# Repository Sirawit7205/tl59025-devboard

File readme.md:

# TLC59025 Devboard

This is an open-source KiCAD design files for a development for [Texas Instruments TLC59025](https://www.ti.com/lit/ds/symlink/tlc59025.pdf) 16-Channel Constant Current LED Driver (and clones).

## Pictures

## Features

This devboard provides full flexibility for testing various configurations of the chip and surrounding circuits.

- Support original and clones in QSOP-24 package:
	- TI TLC59025IDBQR
	- Macroblock MBI5124GP
	- Shenzhen Sunmoon SM16206S
	- Shenzhen Sunmoon SM16306S
	- Shenzhen Titan TM5020A
- Full control over the chip's functions:
	- Output LEDs on all output channels.
	- R-EXT trimpot on each chip for adjusting the sink current.
	- All control pins break out.
- Cascade design
	- Input and output headers provided for cascading of modules (allows single controller only).
- Multiple power options
	- USB Type-C
	- Input header (both regulated and unregulated)
	- Optional footprint for an LDO.
- Onboard Microcontroller
	- Optional footprint for ATtiny214/414/814.
	- A user button and several debug pads provided.
	- A CH340 bridge for serial communication with a computer.
	- UPDI Header included.
	- SerialUPDI support included.
	
## Revisions

We are currently at Revision 1. Changelog is below:

**Revision 1 (September 2022)**
 - Initial Design

## What is provided

The goal of this repository is to enable you to build this on your own as easy as possible (although I originally plan to sell this as a kit as well). **The schematics, PCB design, and an interactive BOM is provided.**

Hardware is licensed under `SPDX-License-Identifier: CERN-OHL-S-2.0`

Software is licensed under `SPDX-License-Identifier: GPL` (Actually there is no software for this board. Oops.)

Documentation is licensed under `SPDX-License-Identifier: CC-BY-SA-4.0`

**This project is an OSHWA Certified Open Source Hardware Project with UID [TH000010](https://certification.oshwa.org/th000010.html).**

3D models that are use to render the board in KiCAD is not included. They are all from GrabCad and you could search and download them by yourself.

## Third-Party 3D Models

- 6x3.5mm Tactile Button by Gabriel Tóth: https://grabcad.com/library/6x3-5mm-smd-tactile-button-1
- Bourns 3362P Trimpot by Markus Walter: https://grabcad.com/library/bourns-3362p-1-102lf
- USB Type-C port by Hamza Huzair: https://grabcad.com/library/usb-type-c-port-smd-type-1
 
 ## Ordering
 
 You can export gerbers from this project and order the board yourself. You can also use the link below to directly order from Aisler.
 https://aisler.net/p/IMLSHTDQ

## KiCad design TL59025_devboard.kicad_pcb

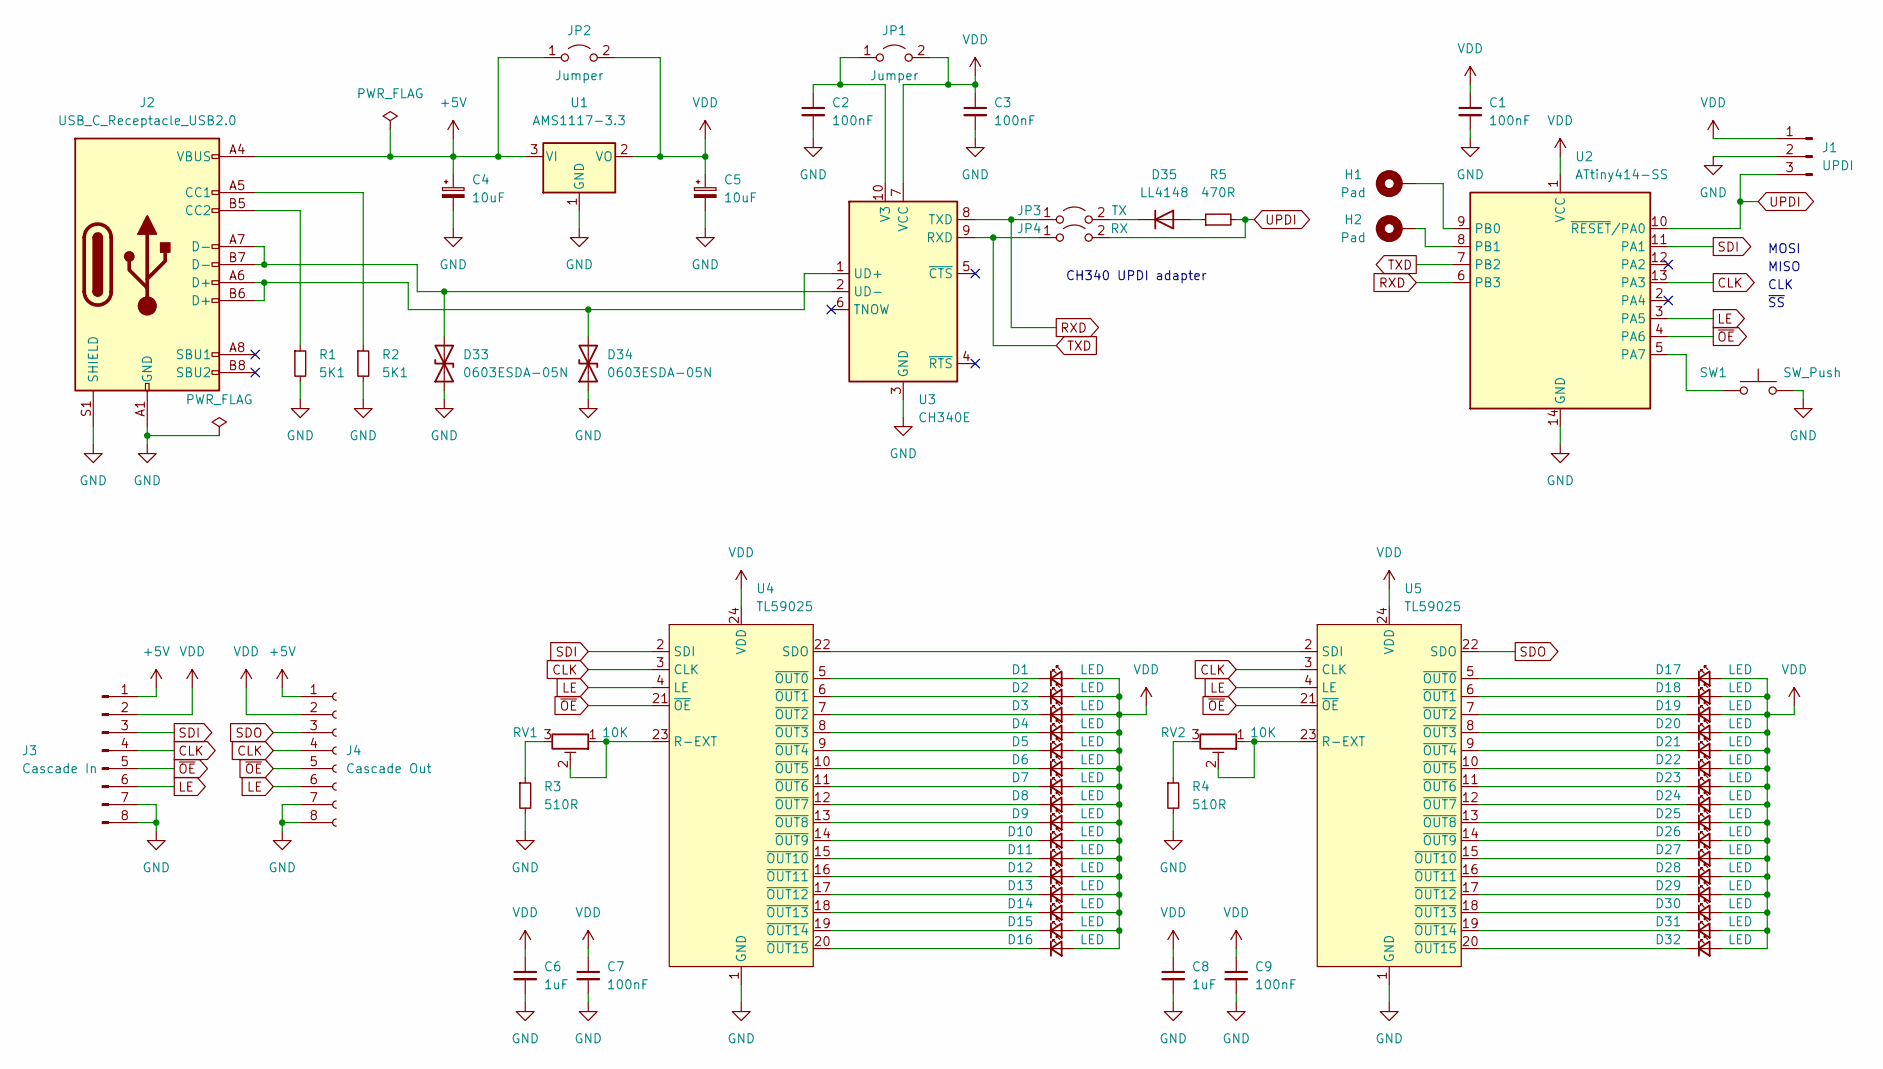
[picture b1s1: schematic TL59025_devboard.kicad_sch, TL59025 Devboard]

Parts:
C1, C2, C3, C7, C9: 100nF; C_0603_1608Metric
C4, C5: 10uF; CP_Radial_D5.0mm_P2.00mm
C6, C8: 1uF; C_0603_1608Metric
D1, D2, D3, D4, D5, D6, D7, D8, D9, D10, D11, D12, D13, D14, D15, D16, D17, D18, D19, D20, D21, D22, D23, D24, D25, D26, D27, D28, D29, D30, D31, D32: LED; LED_0805_2012Metric
D33, D34: 0603ESDA-05N; D_0603_1608Metric
D35: LL4148; D_MiniMELF
H1, H2: Pad; TestPoint_Pad_D1.0mm
J1: UPDI; PinHeader_1x03_P2.54mm_Vertical
J2: USB_C_Receptacle_USB2.0; USB_C_Receptacle_HRO_TYPE-C-31-M-12_NO_SBU_CircularHoles
J3: Cascade In; PinHeader_1x08_P2.54mm_Vertical
J4: Cascade Out; PinSocket_1x08_P2.54mm_Vertical
JP1, JP2: Jumper; SolderJumper-2_P1.3mm_Open_Pad1.0x1.5mm
JP3: TX; PinHeader_1x02_P2.54mm_Vertical
JP4: RX; PinHeader_1x02_P2.54mm_Vertical
R1, R2: 5K1; R_0603_1608Metric
R3, R4: 510R; R_0603_1608Metric
R5: 470R; R_0603_1608Metric
RV1, RV2: 10K; 3362P_1
SW1: SW_Push; TS-1101
U1: AMS1117-3.3; SOT-223-3_TabPin2
U2: ATtiny414-SS; SOIC-14_3.9x8.7mm_P1.27mm
U3: CH340E; MSOP-10_3x3mm_P0.5mm
U4, U5: TL59025; QSOP-24_3.9x8.7mm_P0.635mm

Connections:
+5V: C4.1, J2.A4 (VBUS), J2.A9 (VBUS), J2.B4 (VBUS), J2.B9 (VBUS), J3.1, J4.1, JP2.1 (A), U1.3 (VI)
CLK: J3.4, J4.4, U2.13 (PA3), U4.3 (CLK), U5.3 (CLK)
GND: C1.2, C2.2, C3.2, C4.2, C5.2, C6.2, C7.2, C8.2, C9.2, D33.1 (A1), D34.1 (A1), J1.2, J2.A1 (GND), J2.A12 (GND), J2.B1 (GND), J2.B12 (GND), J2.S1 (SHIELD), J3.7, J3.8, J4.7, J4.8, R1.2, R2.2, R3.2, R4.2, SW1.2, U1.1 (GND), U2.14 (GND), U3.3 (GND), U4.1 (GND), U5.1 (GND)
LE: J3.6, J4.6, U2.3 (PA5), U4.4 (LE), U5.4 (LE)
unnamed: C2.1, JP1.1 (A), U3.10 (V3)
unnamed: D1.1 (K), U4.5 (~OUT0)
unnamed: D2.1 (K), U4.6 (~OUT1)
unnamed: D3.1 (K), U4.7 (~OUT2)
unnamed: D4.1 (K), U4.8 (~OUT3)
unnamed: D5.1 (K), U4.9 (~OUT4)
unnamed: D6.1 (K), U4.10 (~OUT5)
unnamed: D7.1 (K), U4.11 (~OUT6)
unnamed: D8.1 (K), U4.12 (~OUT7)
unnamed: D9.1 (K), U4.13 (~OUT8)
unnamed: D10.1 (K), U4.14 (~OUT9)
unnamed: D11.1 (K), U4.15 (~OUT10)
unnamed: D12.1 (K), U4.16 (~OUT11)
unnamed: D13.1 (K), U4.17 (~OUT12)
unnamed: D14.1 (K), U4.18 (~OUT13)
unnamed: D15.1 (K), U4.19 (~OUT14)
unnamed: D16.1 (K), U4.20 (~OUT15)
unnamed: D17.1 (K), U5.5 (~OUT0)
unnamed: D18.1 (K), U5.6 (~OUT1)
unnamed: D19.1 (K), U5.7 (~OUT2)
unnamed: D20.1 (K), U5.8 (~OUT3)
unnamed: D21.1 (K), U5.9 (~OUT4)
unnamed: D22.1 (K), U5.10 (~OUT5)
unnamed: D23.1 (K), U5.11 (~OUT6)
unnamed: D24.1 (K), U5.12 (~OUT7)
unnamed: D25.1 (K), U5.13 (~OUT8)
unnamed: D26.1 (K), U5.14 (~OUT9)
unnamed: D27.1 (K), U5.15 (~OUT10)
unnamed: D28.1 (K), U5.16 (~OUT11)
unnamed: D29.1 (K), U5.17 (~OUT12)
unnamed: D30.1 (K), U5.18 (~OUT13)
unnamed: D31.1 (K), U5.19 (~OUT14)
unnamed: D32.1 (K), U5.20 (~OUT15)
unnamed: D33.2 (A2), J2.A7 (D-), J2.B7 (D-), U3.2 (UD-)
unnamed: D34.2 (A2), J2.A6 (D+), J2.B6 (D+), U3.1 (UD+)
unnamed: D35.1 (K), JP3.2 (B)
unnamed: D35.2 (A), R5.1
unnamed: H1.1, U2.9 (PB0)
unnamed: H2.1, U2.8 (PB1)
unnamed: J2.A5 (CC1), R2.1
unnamed: J2.B5 (CC2), R1.1
unnamed: R3.1, RV1.3
unnamed: R4.1, RV2.3
unnamed: RV1.1, RV1.2, U4.23 (R-EXT)
unnamed: RV2.1, RV2.2, U5.23 (R-EXT)
unnamed: SW1.1, U2.5 (PA7)
unnamed: U4.22 (SDO), U5.2 (SDI)
RXD: JP3.1 (A), U2.6 (PB3), U3.8 (TXD)
SDI: J3.3, U2.11 (PA1), U4.2 (SDI)
SDO: J4.3, U5.22 (SDO)
TXD: JP4.1 (A), U2.7 (PB2), U3.9 (RXD)
UPDI: J1.3, JP4.2 (B), R5.2, U2.10 (~RESET/PA0)
VDD: C1.1, C3.1, C5.1, C6.1, C7.1, C8.1, C9.1, D1.2 (A), D2.2 (A), D3.2 (A), D4.2 (A), D5.2 (A), D6.2 (A), D7.2 (A), D8.2 (A), D9.2 (A), D10.2 (A), D11.2 (A), D12.2 (A), D13.2 (A), D14.2 (A), D15.2 (A), D16.2 (A), D17.2 (A), D18.2 (A), D19.2 (A), D20.2 (A), D21.2 (A), D22.2 (A), D23.2 (A), D24.2 (A), D25.2 (A), D26.2 (A), D27.2 (A), D28.2 (A), D29.2 (A), D30.2 (A), D31.2 (A), D32.2 (A), J1.1, J3.2, J4.2, JP1.2 (B), JP2.2 (B), U1.2 (VO), U2.1 (VCC), U3.7 (VCC), U4.24 (VDD), U5.24 (VDD)
~OE: J3.5, J4.5, U2.4 (PA6), U4.21 (~OE), U5.21 (~OE)

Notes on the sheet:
~{SS}
CH340 UPDI adapter
CLK
MISO
MOSI

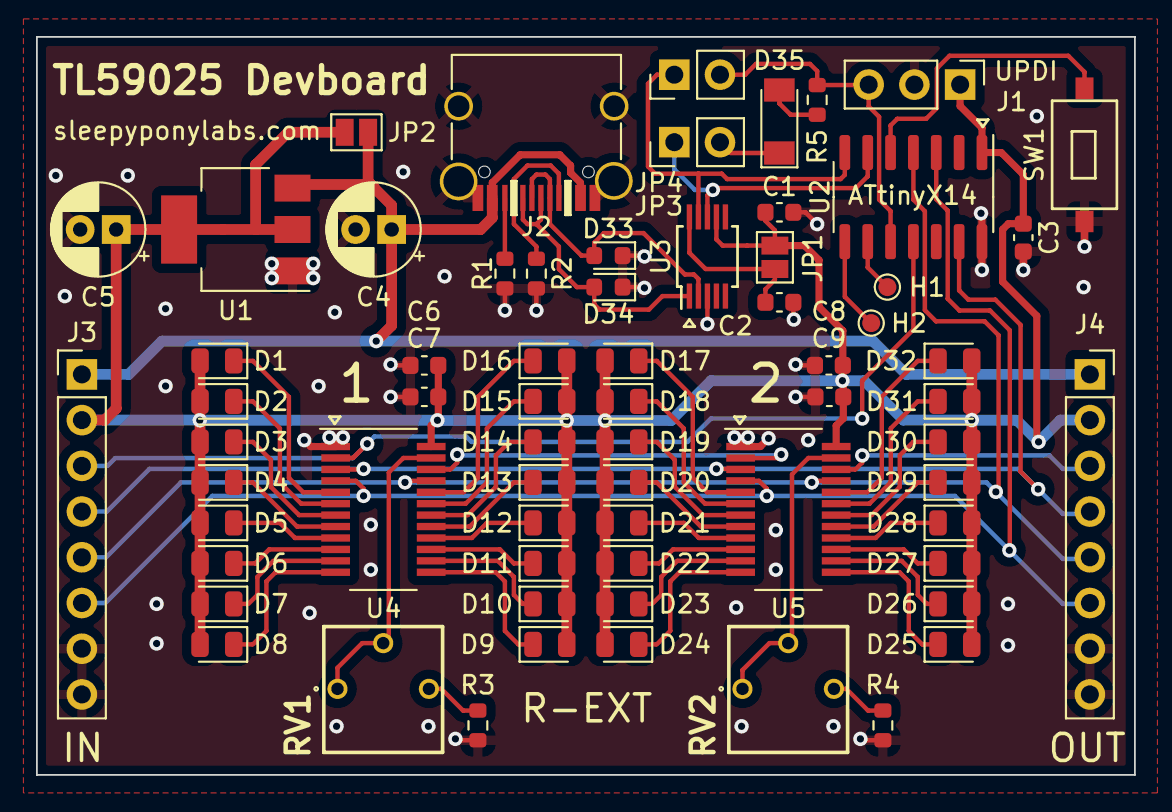
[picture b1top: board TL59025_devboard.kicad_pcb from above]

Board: 2 copper layers, 61.0 x 41.0 mm, 67 parts (0 on the bottom side), 58 nets.

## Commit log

2022-09-18 Add IBOM and render images
2022-09-24 Add license and readme
2023-01-11 Change R3 and R4 to 510R for maximum current range
2023-05-25 Update readme.md
    Edit licenses and add OSHWA info.
2023-05-28 Update LICENSE
